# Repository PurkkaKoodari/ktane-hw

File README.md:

# KTaNE HW

This project is a hardware reimplementation of the game [Keep Talking and Nobody Explodes][ktane]. The game runs fully on the physical device and is controlled using a web interface over Wi-Fi. The project will be documented in this repository &ndash; expect the links below to be broken for the near future.

(TODO: insert photos here)

## Architecture

The hardware is built around a Raspberry Pi Zero W, which runs the main controller software, attached to a [backplane](doc/hardware/backplane.md) that provides power, connectivity and audio. The game's [modules](doc/hardware/modules.md) are built as independent devices, usually based on an Arduino Nano, which connect to the backplane using RJ-45 connectors (with a completely nonstandard usage of the pins).

The software can be divided into three parts: the [main controller](doc/software/main_controller.md), written in Python 3 using `asyncio` and [`websockets`][websockets]; the module software, written in C++ and built using [`arduino-cli`][arduino-cli]; and the Web interface, written using [Preact][preact]. In addition, one can run a [room server](doc/software/room_server.md), which supports room-scale audio and DMX lights and other effects.

## License

Unless otherwise noted, all software in this repository is licensed under the [MIT license](LICENSE); the hardware design files in `hardware/` are licensed under the [CERN-OHL-P v2](hardware/LICENSE); and the sounds in `sounds/` are licensed under CC-BY 3.0 (see [sounds/CREDITS.txt](sounds/CREDITS.txt) for authors).

This project is not in any way related to or endorsed by Steel Crate Games, nor does it include any assets from the original game. If you intend to build a copy of the project, please support them and [purchase a copy of the game][buy-ktane]!

[ktane]: http://www.keeptalkinggame.com/
[buy-ktane]: https://keeptalkinggame.com/#buynow
[websockets]: https://websockets.readthedocs.io/en/stable/intro.html
[arduino-cli]: https://arduino.github.io/arduino-cli/latest/commands/arduino-cli/
[preact]: https://preactjs.com/

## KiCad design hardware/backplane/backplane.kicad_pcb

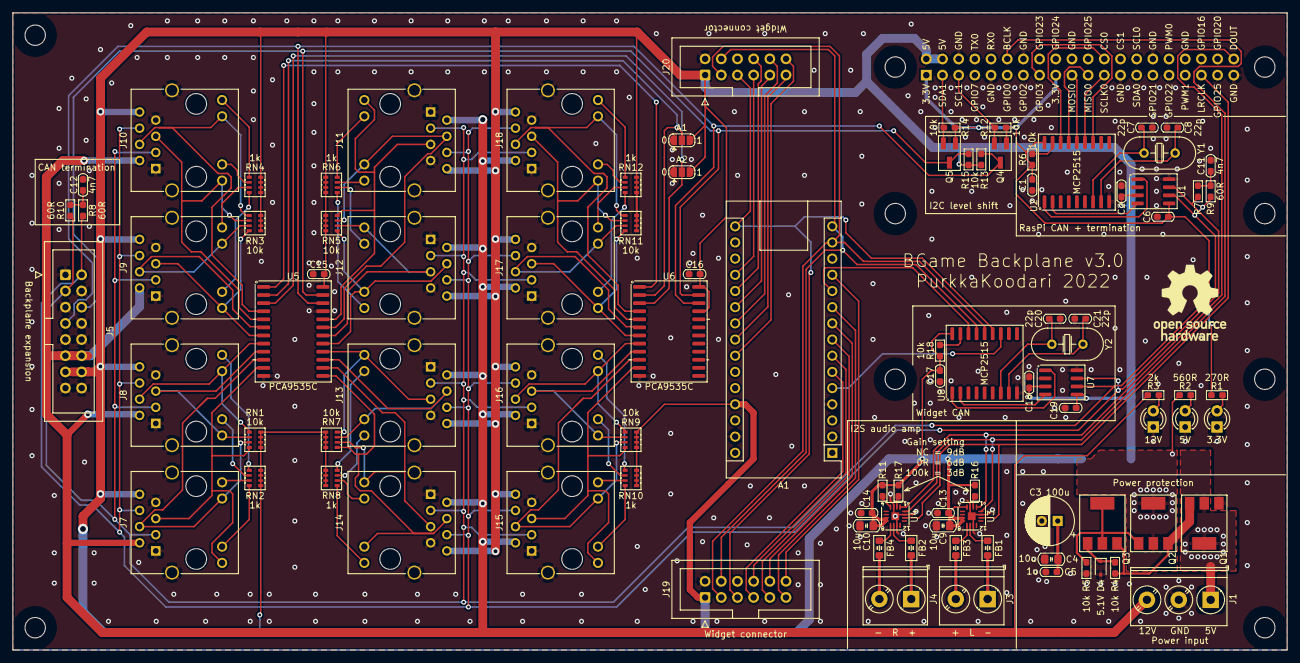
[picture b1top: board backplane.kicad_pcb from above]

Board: 2 copper layers, 200.0 x 100.0 mm, 103 parts (1 on the bottom side), 116 nets.

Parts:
A1: Arduino_Nano_v3.x; Arduino_Nano
C1, C2, C6, C13, C14, C15, C16, C17, C18, C19: 100n; C_0603_1608Metric_Pad1.08x0.95mm
C3: 100u; CP_Radial_D7.5mm_P2.50mm
C4, C9, C10: 10u; C_0805_2012Metric_Pad1.18x1.45mm
C5: 1u; C_0603_1608Metric_Pad1.08x0.95mm
C7, C8, C20, C21: 22p; C_0603_1608Metric_Pad1.08x0.95mm
C11, C12: 4n7; C_0603_1608Metric_Pad1.08x0.95mm
D1, D2, D3: LED; LED_D3.0mm
D4: BZX384-5V1; D_SOD-323
FB1, FB2, FB3, FB4: Ferrite_Bead; Ferrite_0805_2012Metric_Pad1.05x1.20mm_BigPads
H_RPI1, H_RPI2: RPi_HDR; MountingHole_3.2mm_M3
H_RPI3, H_RPI4: RPi_ZERO; MountingHole_3.2mm_M3
H_RPI5, H_RPI6: RPi_3; MountingHole_3.2mm_M3
J1: Screw_Terminal_01x03; TerminalBlock_Phoenix_PT-1,5-3-5.0-H_1x03_P5.00mm_Horizontal
J2: Raspberry_Pi_2_3; PinSocket_2x20_P2.54mm_Vertical
J3, J4: Screw_Terminal_01x02; TerminalBlock_Phoenix_PT-1,5-2-5.0-H_1x02_P5.00mm_Horizontal
J5: Conn_02x08_Odd_Even; IDC-Header_2x08_P2.54mm_Vertical
J7, J8, J9, J10, J11, J12, J13, J14, J15, J16, J17, J18: RJ45_LED_Shielded; RJ45_RCH5242CB
J19, J20: Conn_02x06_Odd_Even; IDC-Header_2x06_P2.54mm_Vertical
JP1: GPIO_A1; SolderJumper-3_P1.3mm_Open_RoundedPad1.0x1.5mm
JP2: GPIO_A2; SolderJumper-3_P1.3mm_Open_RoundedPad1.0x1.5mm
LOGO1: Logo_Open_Hardware_Small; OSHW-Logo_11.4x12mm_SilkScreen
Q1, Q2, Q3: ZXMP4A16G; SOT-223-3_TabPin2
Q4, Q5: Q_NMOS_GSD; SOT-23_Handsoldering
R1: 270R; R_0603_1608Metric_Pad1.05x0.95mm
R2: 560R; R_0603_1608Metric_Pad1.05x0.95mm
R3: 2k; R_0603_1608Metric_Pad1.05x0.95mm
R4, R5, R6, R12, R13, R14, R15, R18: 10k; R_0603_1608Metric_Pad1.05x0.95mm
R7, R8, R9, R10: 60R; R_0603_1608Metric_Pad1.05x0.95mm
R11: 330k; R_0603_1608Metric_Pad1.05x0.95mm
R16, R17: 100k; R_0603_1608Metric_Pad1.05x0.95mm
RN1, RN3, RN5, RN7, RN9, RN11: 10k; R_Array_Convex_4x0603
RN2, RN4, RN6, RN8, RN10, RN12: 1k; R_Array_Convex_4x0603
U1, U7: TJA1051T/3; SOIC-8_3.9x4.9mm_P1.27mm
U2, U8: MCP2515-xSO; SOIC-18W_7.5x11.6mm_P1.27mm
U3, U4: MAX98357AETE; TQFN-16-1EP_3x3mm_P0.5mm_EP1.23x1.23mm
U5, U6: PCA9535C; SOIC-24W_7.5x15.4mm_P1.27mm
Y1, Y2: 8MHz; Crystal_HC49-U_Vertical

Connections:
+3V3: C1.1, C6.1, J2.1 (3V3), J2.17 (3V3), Q4.1 (G), Q5.1 (G), R1.1, R6.1, R12.1, R14.1, U1.5 (VIO), U2.18 (VDD)
+5V: J1.1, Q1.2 (D)
+12V: J1.3, J5.11, J5.12, J7.2, J8.2, J9.2, J10.2, J11.2, J12.2, J13.2, J14.2, J15.2, J16.2, J17.2, J18.2, R3.1
/CAN_CS: J2.24 (~CE0/GPIO8), U2.16 (~CS)
/CAN_INT: J2.15 (GPIO22), U2.12 (~INT)
/GPIO_ADDR1: JP1.2 (C), U5.2 (A1), U6.2 (A1)
/GPIO_ADDR2: JP2.2 (C), U5.3 (A2), U6.3 (A2)
/GPIO_INT: U5.1 (~INT), U6.1 (~INT)
/MISO_3V3: J2.21 (MISO0/GPIO9), U2.15 (SO)
/MODULE_LOCATE_0: J7.4, J7.11, RN1.7 (R2.2), U5.10 (IO0_6)
/MODULE_LOCATE_1: J8.4, J8.11, RN1.5 (R4.2), U5.8 (IO0_4)
/MODULE_LOCATE_2: J9.4, J9.11, RN3.7 (R2.2), U5.6 (IO0_2)
/MODULE_LOCATE_3: J10.4, J10.11, RN3.5 (R4.2), U5.4 (IO0_0)
/MODULE_LOCATE_4: J11.4, J11.11, RN5.7 (R2.2), U5.19 (IO1_6)
/MODULE_LOCATE_5: J12.4, J12.11, RN5.5 (R4.2), U5.17 (IO1_4)
/MODULE_LOCATE_6: J13.4, J13.11, RN7.7 (R2.2), U5.15 (IO1_2)
/MODULE_LOCATE_7: J14.4, J14.11, RN7.5 (R4.2), U5.13 (IO1_0)
/MODULE_LOCATE_8: J15.4, J15.11, RN9.7 (R2.2), U6.10 (IO0_6)
/MODULE_LOCATE_9: J16.4, J16.11, RN9.5 (R4.2), U6.8 (IO0_4)
/MODULE_LOCATE_10: J17.4, J17.11, RN11.7 (R2.2), U6.6 (IO0_2)
/MODULE_LOCATE_11: J18.4, J18.11, RN11.5 (R4.2), U6.4 (IO0_0)
/MODULE_SENSE_0: J7.5, J7.9, RN1.8 (R1.2), U5.11 (IO0_7)
/MODULE_SENSE_1: J8.5, J8.9, RN1.6 (R3.2), U5.9 (IO0_5)
/MODULE_SENSE_2: J9.5, J9.9, RN3.8 (R1.2), U5.7 (IO0_3)
/MODULE_SENSE_3: J10.5, J10.9, RN3.6 (R3.2), U5.5 (IO0_1)
/MODULE_SENSE_4: J11.5, J11.9, RN5.8 (R1.2), U5.20 (IO1_7)
/MODULE_SENSE_5: J12.5, J12.9, RN5.6 (R3.2), U5.18 (IO1_5)
/MODULE_SENSE_6: J13.5, J13.9, RN7.8 (R1.2), U5.16 (IO1_3)
/MODULE_SENSE_7: J14.5, J14.9, RN7.6 (R3.2), U5.14 (IO1_1)
/MODULE_SENSE_8: J15.5, J15.9, RN9.8 (R1.2), U6.11 (IO0_7)
/MODULE_SENSE_9: J16.5, J16.9, RN9.6 (R3.2), U6.9 (IO0_5)
/MODULE_SENSE_10: J17.5, J17.9, RN11.8 (R1.2), U6.7 (IO0_3)
/MODULE_SENSE_11: J18.5, J18.9, RN11.6 (R3.2), U6.5 (IO0_1)
/MOSI_3V3: J2.19 (MOSI0/GPIO10), U2.14 (SI)
/PCM_BCLK: J2.12 (GPIO18/PWM0), U3.16 (BCLK), U4.16 (BCLK)
/PCM_DOUT: J2.40 (GPIO21/SCLK1), U3.1 (DIN), U4.1 (DIN)
/PCM_LRCLK: J2.35 (GPIO19/MISO1), U3.14 (LRCLK), U4.14 (LRCLK)
/SCL: J5.7, Q4.3 (D), R13.2, U5.22 (SCL), U6.22 (SCL)
/SCLK_3V3: J2.23 (SCLK0/GPIO11), U2.13 (SCK)
/SCL_3V3: J2.5 (SCL/GPIO3), Q4.2 (S), R12.2
/SDA: J5.6, Q5.3 (D), R15.2, U5.23 (SDA), U6.23 (SDA)
/SDA_3V3: J2.3 (SDA/GPIO2), Q5.2 (S), R14.2
/SPKR_L+: FB3.2, J3.2
/SPKR_L-: FB1.2, J3.1
/SPKR_R+: FB4.2, J4.2
/SPKR_R-: FB2.2, J4.1
/WIDGET_CAN_CS: A1.11 (D8), U8.16 (~CS)
/WIDGET_CAN_INT: A1.5 (D2), U8.12 (~INT)
/WIDGET_CS0: A1.6 (D3), J19.7
/WIDGET_CS1: A1.7 (D4), J19.8
/WIDGET_CS2: A1.8 (D5), J19.9
/WIDGET_CS3: A1.9 (D6), J19.10
/WIDGET_CS4: A1.10 (D7), J19.11
/WIDGET_CS5: A1.12 (D9), J19.12
/WIDGET_CS6: A1.19 (A0), J20.7
/WIDGET_CS7: A1.20 (A1), J20.8
/WIDGET_CS8: A1.21 (A2), J20.9
/WIDGET_CS9: A1.22 (A3), J20.10
/WIDGET_CS10: A1.23 (A4), J20.11
/WIDGET_CS11: A1.24 (A5), J20.12
/WIDGET_MISO: A1.15 (D12), J19.4, J20.4, U8.15 (SO)
/WIDGET_MOSI: A1.14 (D11), J19.3, J20.3, U8.14 (SI)
/WIDGET_SCLK: A1.16 (D13), J19.5, J20.5, U8.13 (SCK)
CAN_H: J5.2, J7.6, J8.6, J9.6, J10.6, J11.6, J12.6, J13.6, J14.6, J15.6, J16.6, J17.6, J18.6, R7.1, R8.1, U1.7 (CANH), U7.7 (CANH)
CAN_L: J5.3, J7.3, J8.3, J9.3, J10.3, J11.3, J12.3, J13.3, J14.3, J15.3, J16.3, J17.3, J18.3, R9.1, R10.1, U1.6 (CANL), U7.6 (CANL)
GND: A1.4 (GND), A1.29 (GND), C1.2, C2.2, C3.2, C4.2, C5.2, C6.2, C7.2, C8.2, C9.1, C10.1, C11.2, C12.2, C13.1, C14.1, C15.2, C16.2, C17.2, C18.2, C19.2, C20.2, C21.2, D1.1 (K), D2.1 (K), D3.1 (K), D4.2 (A), J1.2, J2.6 (GND), J2.9 (GND), J2.14 (GND), J2.20 (GND), J2.25 (GND), J2.30 (GND), J2.34 (GND), J2.39 (GND), J5.1, J5.4, J5.5, J5.8, J5.9, J5.10, J5.15, J5.16, J7.1, J7.7, J7.SH, J8.1, J8.7, J8.SH, J9.1, J9.7, J9.SH, J10.1, J10.7, J10.SH, J11.1, J11.7, J11.SH, J12.1, J12.7, J12.SH, J13.1, J13.7, J13.SH, J14.1, J14.7, J14.SH, J15.1, J15.7, J15.SH, J16.1, J16.7, J16.SH, J17.1, J17.7, J17.SH, J18.1, J18.7, J18.SH, J19.2, J20.2, JP1.1 (A), JP2.1 (A), Q1.1 (G), R5.2, U1.2 (GND), U1.8 (S), U2.9 (VSS), U3.3 (GND), U3.11 (GND), U3.15 (GND), U3.17 (EP), U4.3 (GND), U4.11 (GND), U4.15 (GND), U4.17 (EP), U5.12 (VSS), U5.21 (A0), U6.12 (VSS), U7.2 (GND), U7.8 (S), U8.9 (VSS)
unnamed: C7.1, U2.7 (OSC2), Y1.1
unnamed: C8.1, U2.8 (OSC1), Y1.2
unnamed: C11.1, R7.2, R9.2
unnamed: C12.1, R8.2, R10.2
unnamed: C20.1, U8.7 (OSC2), Y2.1
unnamed: C21.1, U8.8 (OSC1), Y2.2
unnamed: D1.2 (A), R1.2
unnamed: D2.2 (A), R2.2
unnamed: D3.2 (A), R3.2
unnamed: D4.1 (K), Q3.1 (G), R4.2
unnamed: FB1.1, U3.10 (OUTN)
unnamed: FB2.1, U4.10 (OUTN)
unnamed: FB3.1, U3.9 (OUTP)
unnamed: FB4.1, U4.9 (OUTP)
unnamed: J7.10, RN2.8 (R1.2)
unnamed: J7.12, RN2.7 (R2.2)
unnamed: J8.10, RN2.6 (R3.2)
unnamed: J8.12, RN2.5 (R4.2)
unnamed: J9.10, RN4.8 (R1.2)
unnamed: J9.12, RN4.7 (R2.2)
unnamed: J10.10, RN4.6 (R3.2)
unnamed: J10.12, RN4.5 (R4.2)
unnamed: J11.10, RN6.8 (R1.2)
unnamed: J11.12, RN6.7 (R2.2)
unnamed: J12.10, RN6.6 (R3.2)
unnamed: J12.12, RN6.5 (R4.2)
unnamed: J13.10, RN8.8 (R1.2)
unnamed: J13.12, RN8.7 (R2.2)
unnamed: J14.10, RN8.6 (R3.2)
unnamed: J14.12, RN8.5 (R4.2)
unnamed: J15.10, RN10.8 (R1.2)
unnamed: J15.12, RN10.7 (R2.2)
unnamed: J16.10, RN10.6 (R3.2)
unnamed: J16.12, RN10.5 (R4.2)
unnamed: J17.10, RN12.8 (R1.2)
unnamed: J17.12, RN12.7 (R2.2)
unnamed: J18.10, RN12.6 (R3.2)
unnamed: J18.12, RN12.5 (R4.2)
unnamed: Q1.3 (S), Q2.3 (S), Q3.3 (S), R4.1
unnamed: Q2.1 (G), Q3.2 (D), R5.1
unnamed: R6.2, U2.17 (~RESET)
unnamed: R11.2, U4.4 (~SD_MODE)
unnamed: R16.2, U3.2 (GAIN_SLOT)
unnamed: R17.2, U4.2 (GAIN_SLOT)
unnamed: R18.2, U8.17 (~RESET)
unnamed: U1.1 (TXD), U2.1 (TXCAN)
unnamed: U1.4 (RXD), U2.2 (RXCAN)
unnamed: U7.1 (TXD), U8.1 (TXCAN)
unnamed: U7.4 (RXD), U8.2 (RXCAN)
VCC: A1.27 (+5V), C2.1, C3.1, C4.1, C5.1, C9.2, C10.2, C13.2, C14.2, C15.1, C16.1, C17.1, C18.1, C19.1, J2.2 (5V), J2.4 (5V), J5.13, J5.14, J7.8, J8.8, J9.8, J10.8, J11.8, J12.8, J13.8, J14.8, J15.8, J16.8, J17.8, J18.8, J19.1, J20.1, JP1.3 (B), JP2.3 (B), Q2.2 (D), R2.1, R11.1, R13.1, R15.1, R16.1, R17.1, R18.1, RN1.1 (R1.1), RN1.2 (R2.1), RN1.3 (R3.1), RN1.4 (R4.1), RN2.1 (R1.1), RN2.2 (R2.1), RN2.3 (R3.1), RN2.4 (R4.1), RN3.1 (R1.1), RN3.2 (R2.1), RN3.3 (R3.1), RN3.4 (R4.1), RN4.1 (R1.1), RN4.2 (R2.1), RN4.3 (R3.1), RN4.4 (R4.1), RN5.1 (R1.1), RN5.2 (R2.1), RN5.3 (R3.1), RN5.4 (R4.1), RN6.1 (R1.1), RN6.2 (R2.1), RN6.3 (R3.1), RN6.4 (R4.1), RN7.1 (R1.1), RN7.2 (R2.1), RN7.3 (R3.1), RN7.4 (R4.1), RN8.1 (R1.1), RN8.2 (R2.1), RN8.3 (R3.1), RN8.4 (R4.1), RN9.1 (R1.1), RN9.2 (R2.1), RN9.3 (R3.1), RN9.4 (R4.1), RN10.1 (R1.1), RN10.2 (R2.1), RN10.3 (R3.1), RN10.4 (R4.1), RN11.1 (R1.1), RN11.2 (R2.1), RN11.3 (R3.1), RN11.4 (R4.1), RN12.1 (R1.1), RN12.2 (R2.1), RN12.3 (R3.1), RN12.4 (R4.1), U1.3 (VCC), U3.4 (~SD_MODE), U3.7 (VDD), U3.8 (VDD), U4.7 (VDD), U4.8 (VDD), U5.24 (VDD), U6.21 (A0), U6.24 (VDD), U7.3 (VCC), U7.5 (VIO), U8.18 (VDD)

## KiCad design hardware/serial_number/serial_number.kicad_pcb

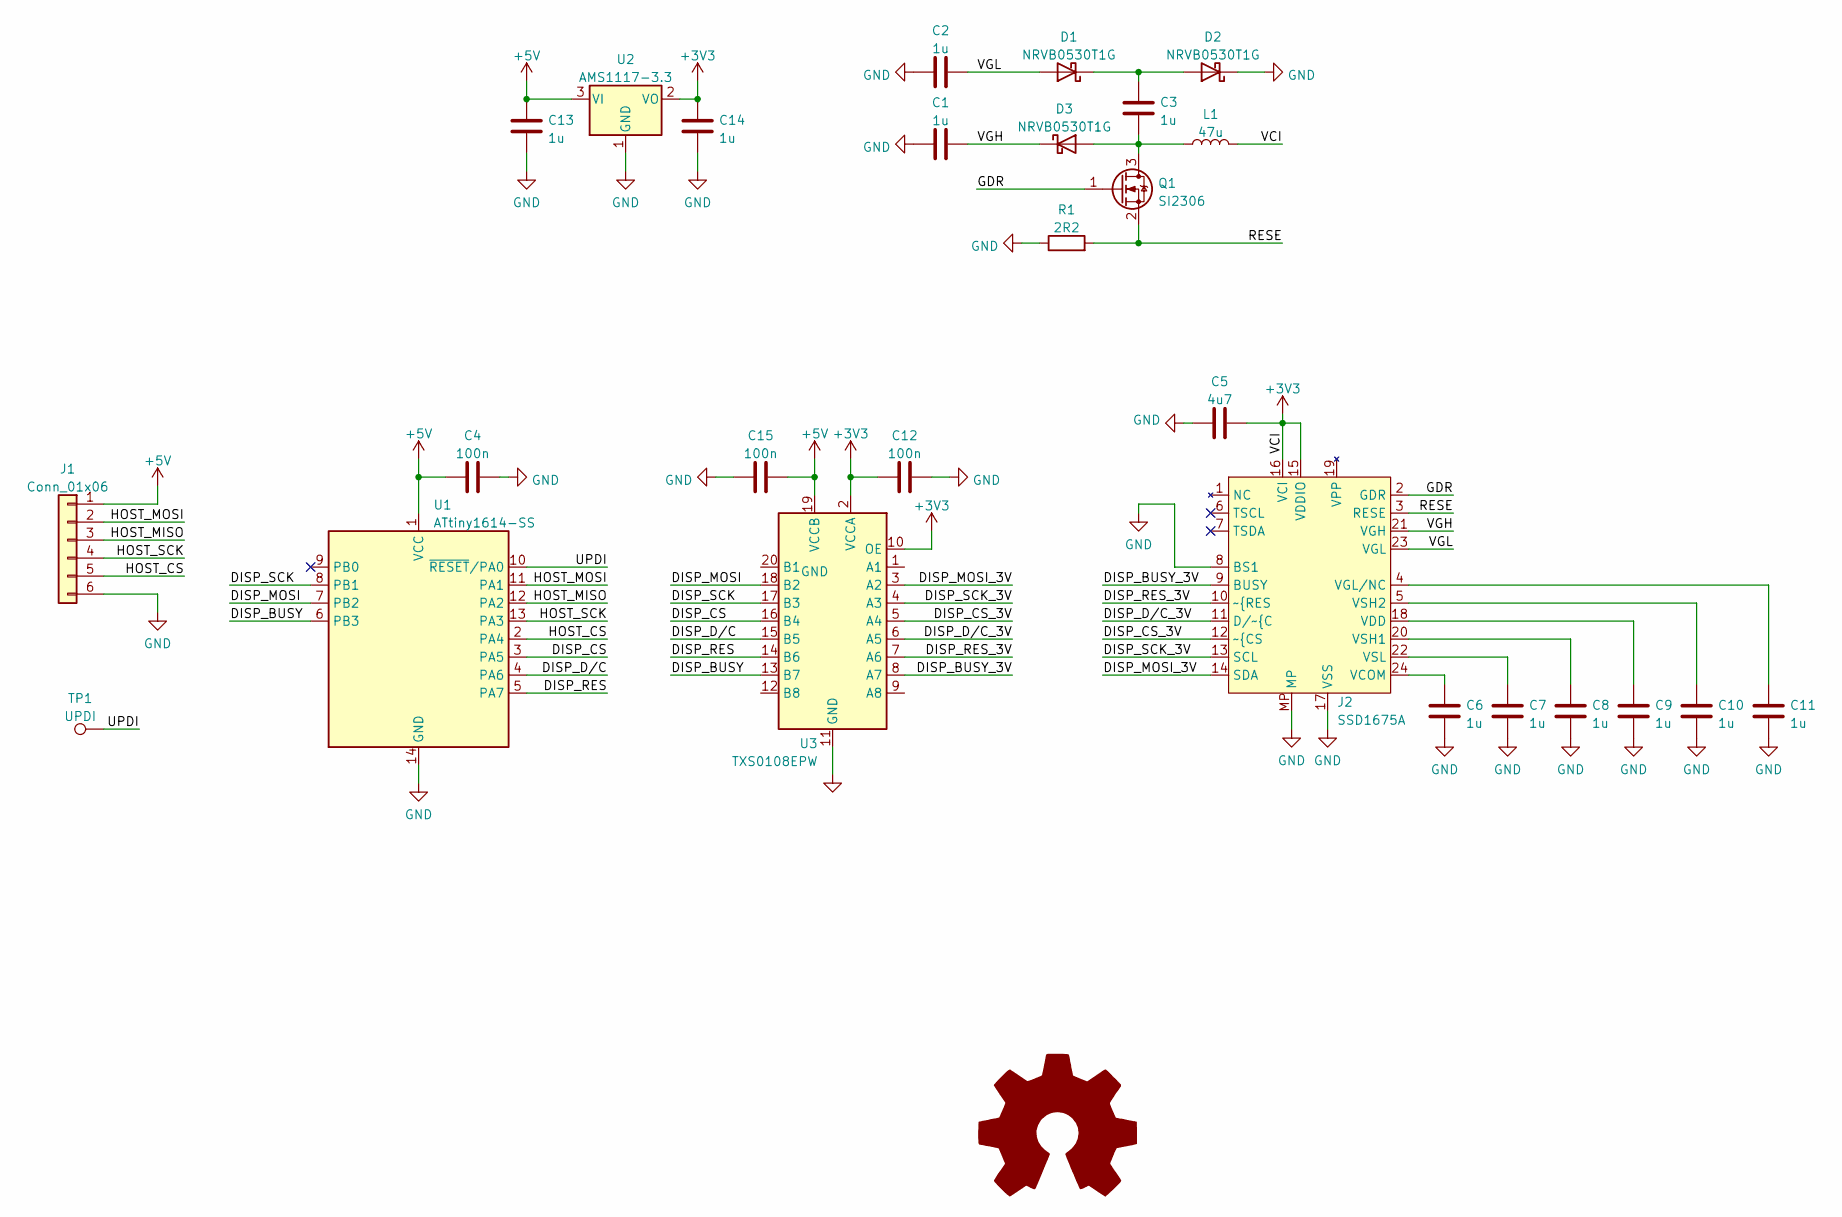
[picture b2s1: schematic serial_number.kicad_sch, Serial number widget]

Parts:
C1, C2, C3, C6, C7, C8, C9, C10, C11, C13, C14: 1u; C_0603_1608Metric_Pad1.08x0.95mm
C4, C12, C15: 100n; C_0603_1608Metric_Pad1.08x0.95mm
C5: 4u7; C_0603_1608Metric_Pad1.08x0.95mm
D1, D2, D3: NRVB0530T1G; D_SOD-123
J1: Conn_01x06; PinHeader_1x06_P2.54mm_Vertical
J2: SSD1675A; ER-CON24HT-1
L1: 47u; L_Taiyo-Yuden_NR-40xx
LOGO1: Logo_Open_Hardware_Large; OSHW-Logo_11.4x12mm_SilkScreen
Q1: SI2306; SOT-23_Handsoldering
R1: 2R2; R_0805_2012Metric_Pad1.20x1.40mm
TP1: UPDI; TestPoint_Pad_D2.5mm
U1: ATtiny1614-SS; SOIC-14_3.9x8.7mm_P1.27mm
U2: AMS1117-3.3; SOT-223-3_TabPin2
U3: TXS0108EPW; TSSOP-20_4.4x6.5mm_P0.65mm

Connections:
+3V3: C5.2, C12.1, C14.2, J2.15 (VDDIO), J2.16 (VCI), L1.2, U2.2 (VO), U3.2 (VCCA), U3.10 (OE)
+5V: C4.1, C13.2, C15.1, J1.1, U1.1 (VCC), U2.3 (VI), U3.19 (VCCB)
/DISP_BUSY: U1.6 (PB3), U3.13 (B7)
/DISP_BUSY_3V: J2.9 (BUSY), U3.8 (A7)
/DISP_CS: U1.3 (PA5), U3.16 (B4)
/DISP_CS_3V: J2.12 (~{CS), U3.5 (A4)
/DISP_D/C: U1.4 (PA6), U3.15 (B5)
/DISP_D/C_3V: J2.11 (D/~{C), U3.6 (A5)
/DISP_MOSI: U1.7 (PB2), U3.18 (B2)
/DISP_MOSI_3V: J2.14 (SDA), U3.3 (A2)
/DISP_RES: U1.5 (PA7), U3.14 (B6)
/DISP_RES_3V: J2.10 (~{RES), U3.7 (A6)
/DISP_SCK: U1.8 (PB1), U3.17 (B3)
/DISP_SCK_3V: J2.13 (SCL), U3.4 (A3)
/GDR: J2.2 (GDR), Q1.1 (G)
/HOST_CS: J1.5, U1.2 (PA4)
/HOST_MISO: J1.3, U1.12 (PA2)
/HOST_MOSI: J1.2, U1.11 (PA1)
/HOST_SCK: J1.4, U1.13 (PA3)
/RESE: J2.3 (RESE), Q1.2 (S), R1.2
/UPDI: TP1.1, U1.10 (~RESET/PA0)
/VGH: C1.2, D3.1 (K), J2.21 (VGH)
/VGL: C2.2, D1.2 (A), J2.23 (VGL)
GND: C1.1, C2.1, C4.2, C5.1, C6.1, C7.1, C8.1, C9.1, C10.1, C11.1, C12.2, C13.1, C14.1, C15.2, D2.1 (K), J1.6, J2.8 (BS1), J2.17 (VSS), J2.MP, R1.1, U1.14 (GND), U2.1 (GND), U3.11 (GND)
unnamed: C3.1, D1.1 (K), D2.2 (A)
unnamed: C3.2, D3.2 (A), L1.1, Q1.3 (D)
unnamed: C6.2, J2.24 (VCOM)
unnamed: C7.2, J2.22 (VSL)
unnamed: C8.2, J2.20 (VSH1)
unnamed: C9.2, J2.18 (VDD)
unnamed: C10.2, J2.5 (VSH2)
unnamed: C11.2, J2.4 (VGL/NC)

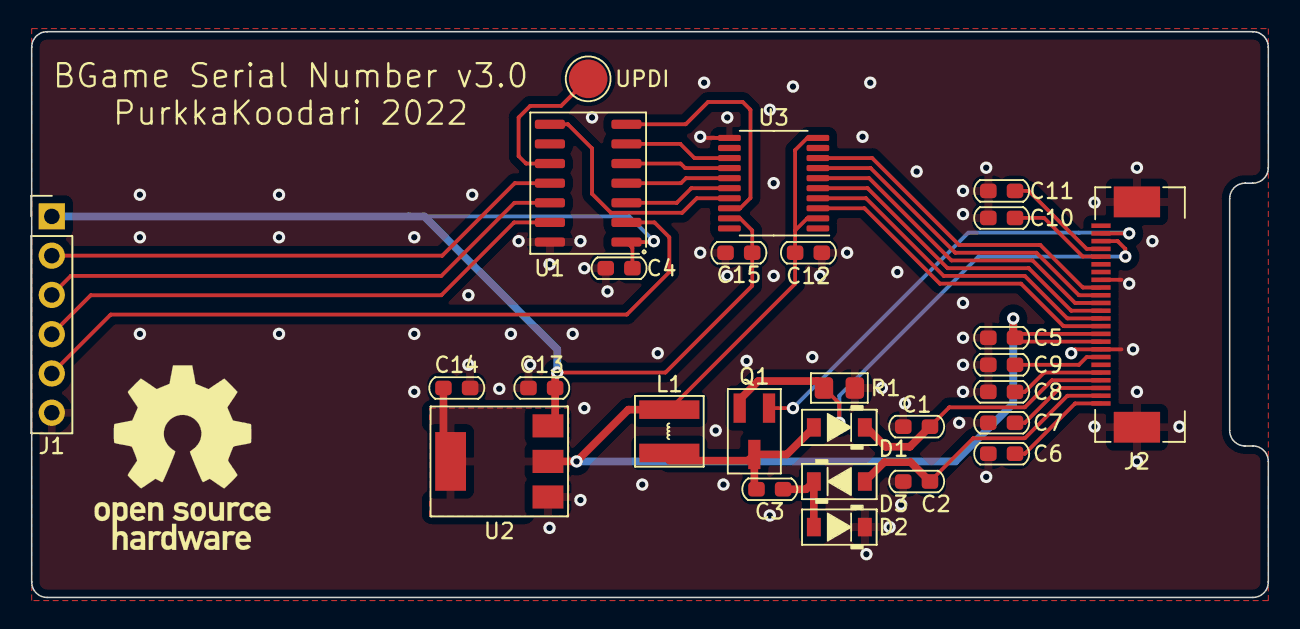
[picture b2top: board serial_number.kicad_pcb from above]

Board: 2 copper layers, 80.0 x 36.6 mm, 28 parts (0 on the bottom side), 32 nets.

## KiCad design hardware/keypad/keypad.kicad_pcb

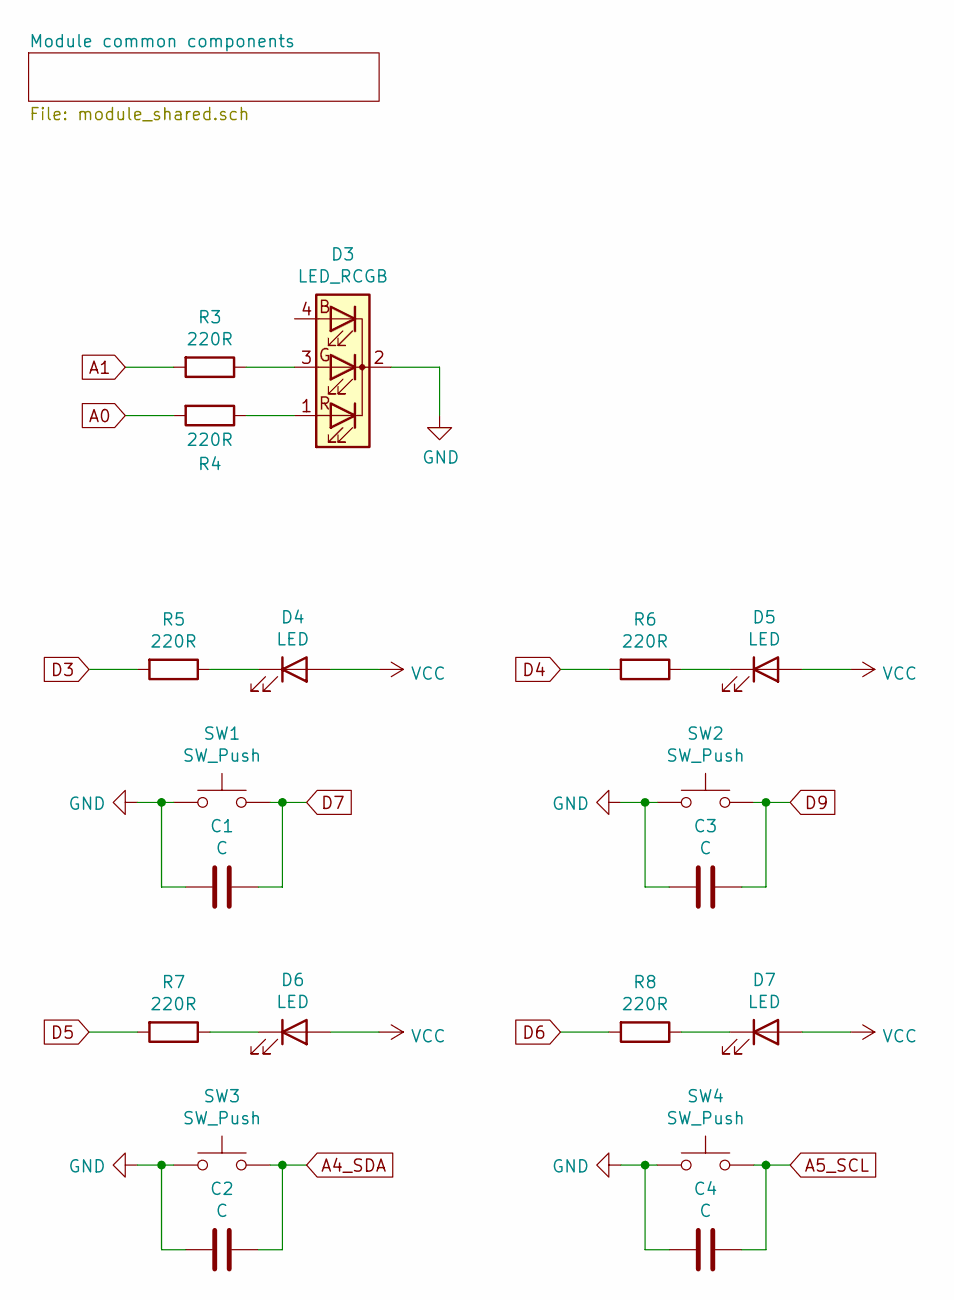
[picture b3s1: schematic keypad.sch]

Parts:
C1, C2, C3, C4: C; C_0805_2012Metric_Pad1.15x1.40mm_HandSolder
D3: LED_RCGB; LED_D5.0mm-4_RGB_Wide_Pins
D4, D5, D6, D7: LED; LED_D3.0mm
R3, R4, R5, R6, R7, R8: 220R; R_0603_1608Metric_Pad1.05x0.95mm_HandSolder
SW1, SW2, SW3, SW4: SW_Push; SW_Cherry_MX_1.00u_PCB

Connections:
A0: R4.2; also elsewhere on the board
A1: R3.2; also elsewhere on the board
A4_SDA: C2.1, SW3.2; also elsewhere on the board
A5_SCL: C4.1, SW4.2; also elsewhere on the board
D3: R5.2; also elsewhere on the board
D4: R6.2; also elsewhere on the board
D5: R7.2; also elsewhere on the board
D6: R8.2; also elsewhere on the board
D7: C1.1, SW1.2; also elsewhere on the board
D9: C3.1, SW2.2; also elsewhere on the board
GND: C1.2, C2.2, C3.2, C4.2, D3.2 (K), SW1.1, SW2.1, SW3.1, SW4.1; also elsewhere on the board
unnamed: D3.1 (RA), R4.1
unnamed: D3.3 (GA), R3.1
unnamed: D4.1 (K), R5.1
unnamed: D5.1 (K), R6.1
unnamed: D6.1 (K), R7.1
unnamed: D7.1 (K), R8.1
VCC: D4.2 (A), D5.2 (A), D6.2 (A), D7.2 (A); also elsewhere on the board

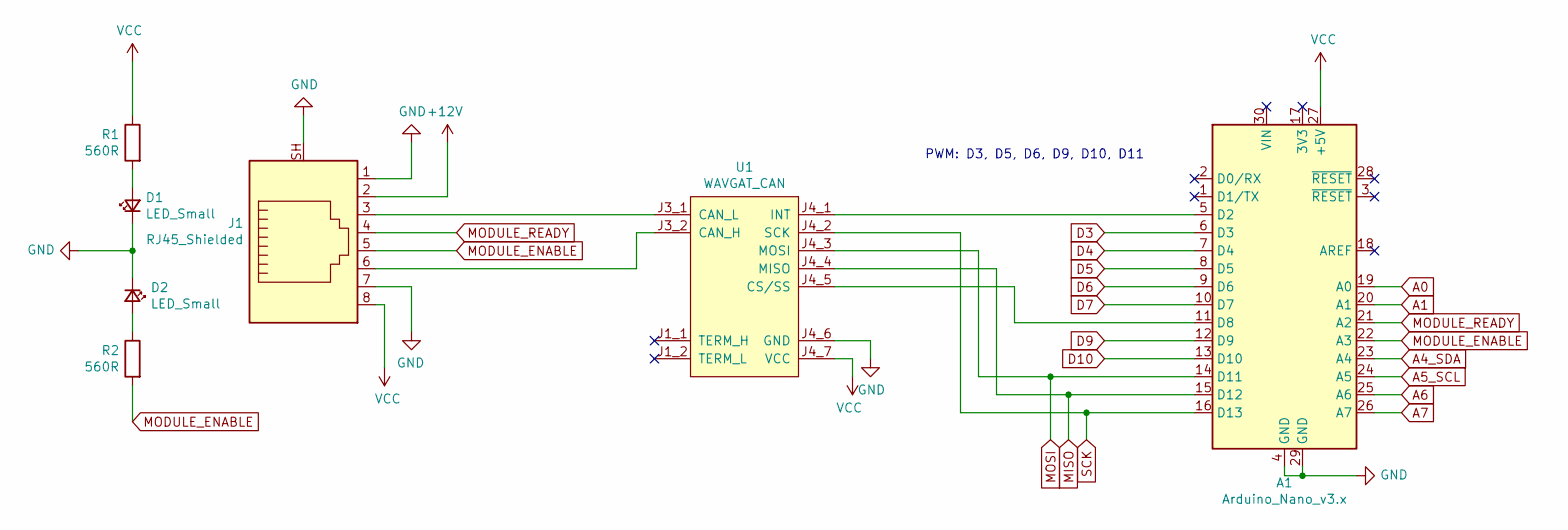
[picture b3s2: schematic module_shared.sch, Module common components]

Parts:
A1: Arduino_Nano_v3.x; Arduino_Nano
D1, D2: LED_Small; LED_D3.0mm
J1: RJ45_Shielded; RJ45_5224
R1, R2: 560R; R_0603_1608Metric_Pad1.05x0.95mm_HandSolder
U1: WAVGAT_CAN

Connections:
+12V: J1.2
A0: A1.19 (A0); also elsewhere on the board
A1: A1.20 (A1); also elsewhere on the board
A4_SDA: A1.23 (A4); also elsewhere on the board
A5_SCL: A1.24 (A5); also elsewhere on the board
A6: A1.25 (A6)
A7: A1.26 (A7)
D3: A1.6 (D3); also elsewhere on the board
D4: A1.7 (D4); also elsewhere on the board
D5: A1.8 (D5); also elsewhere on the board
D6: A1.9 (D6); also elsewhere on the board
D7: A1.10 (D7); also elsewhere on the board
D9: A1.12 (D9); also elsewhere on the board
D10: A1.13 (D10)
GND: A1.4 (GND), A1.29 (GND), D1.1 (K), D2.1 (K), J1.1, J1.7, J1.SH, U1.J4_6 (GND); also elsewhere on the board
MISO: A1.15 (D12), U1.J4_4 (MISO)
MODULE_ENABLE: A1.22 (A3), J1.5, R2.2
MODULE_READY: A1.21 (A2), J1.4
MOSI: A1.14 (D11), U1.J4_3 (MOSI)
unnamed: A1.5 (D2), U1.J4_1 (INT)
unnamed: A1.11 (D8), U1.J4_5 (CS/SS)
unnamed: D1.2 (A), R1.2
unnamed: D2.2 (A), R2.1
unnamed: J1.3, U1.J3_1 (CAN_L)
unnamed: J1.6, U1.J3_2 (CAN_H)
SCK: A1.16 (D13), U1.J4_2 (SCK)
VCC: A1.27 (+5V), J1.8, R1.1, U1.J4_7 (VCC); also elsewhere on the board

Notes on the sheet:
PWM: D3, D5, D6, D9, D10, D11

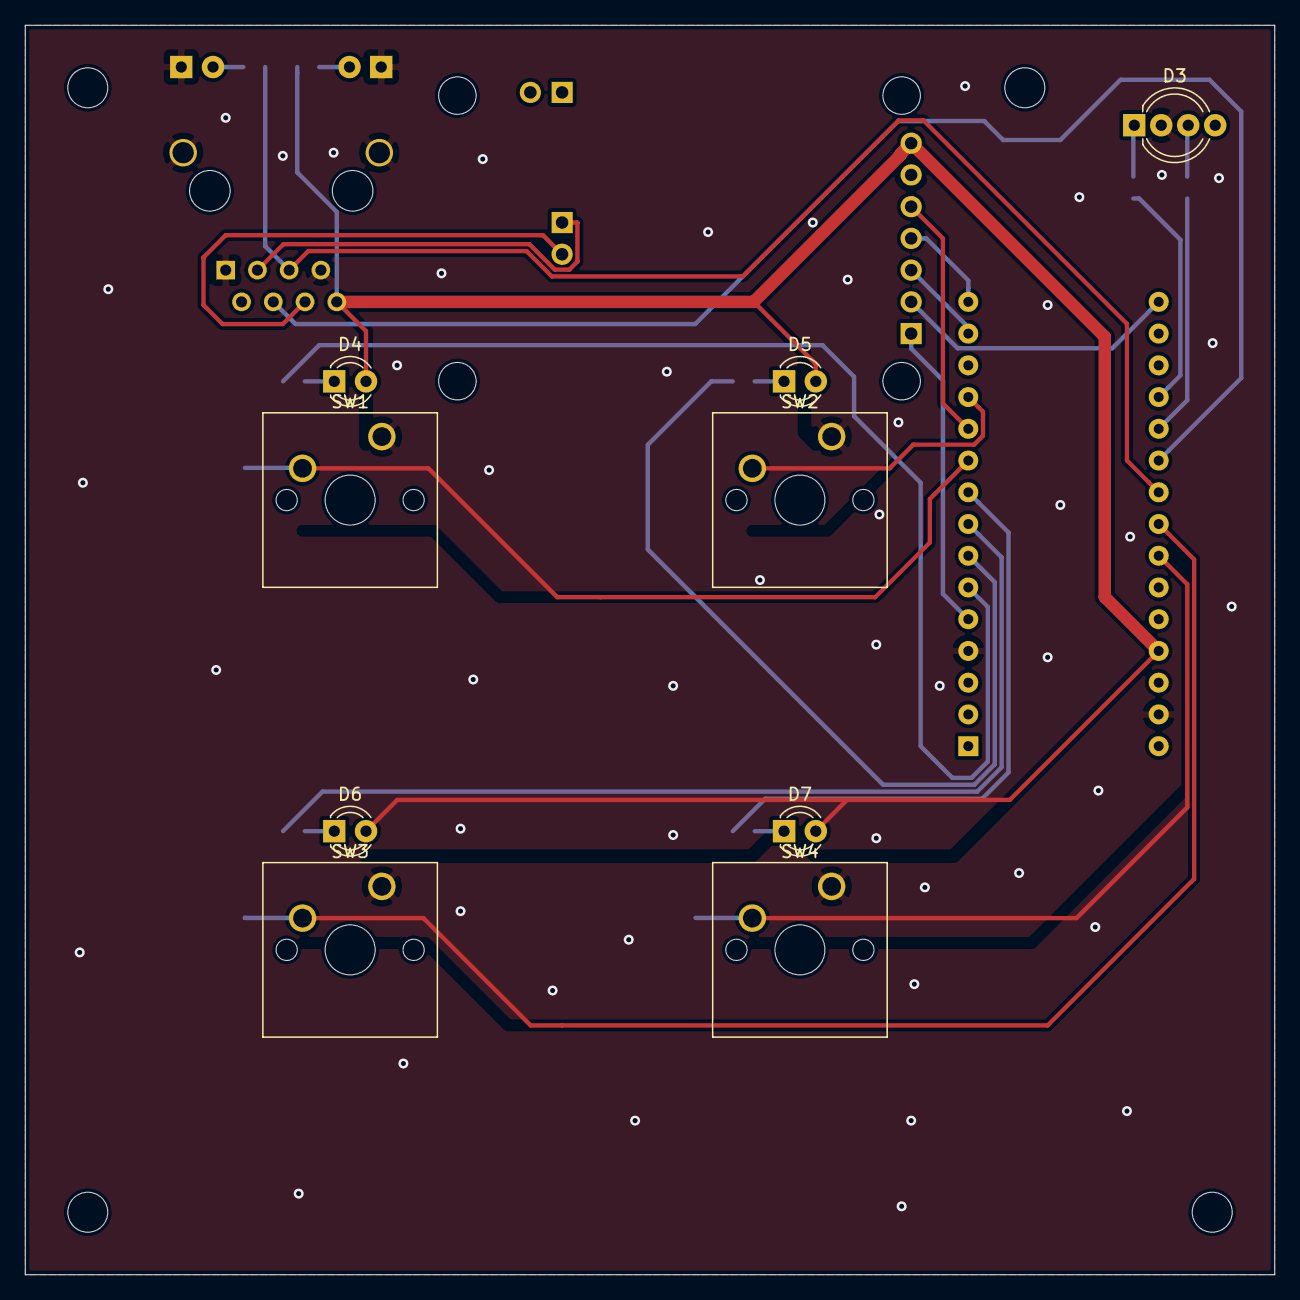
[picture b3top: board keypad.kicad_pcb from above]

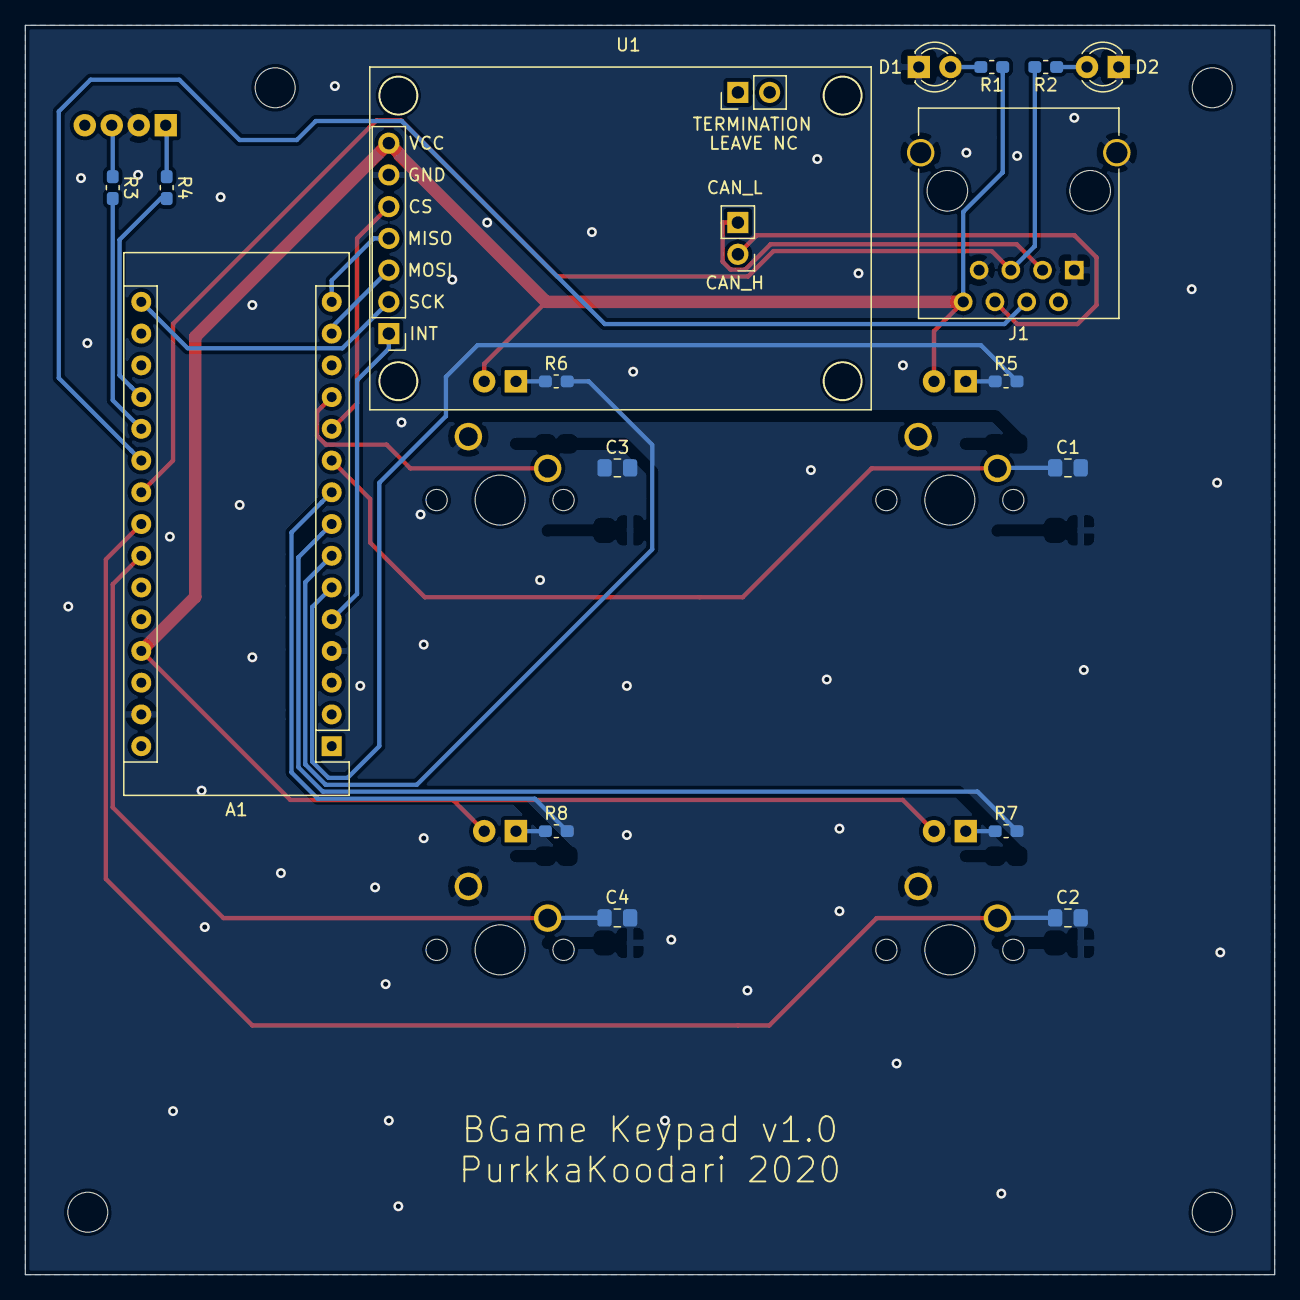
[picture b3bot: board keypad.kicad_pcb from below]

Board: 2 copper layers, 100.0 x 100.0 mm, 26 parts (17 on the bottom side), 29 nets.

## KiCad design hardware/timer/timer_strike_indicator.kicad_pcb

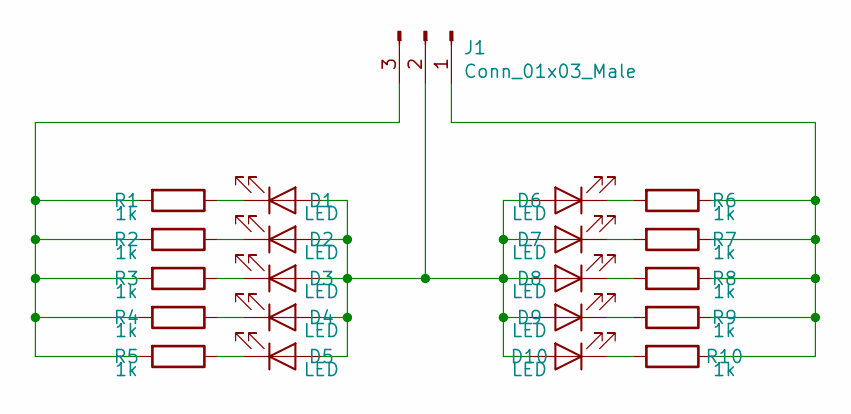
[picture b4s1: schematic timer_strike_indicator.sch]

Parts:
D1, D2, D3, D4, D5, D6, D7, D8, D9, D10: LED; LED_D3.0mm
J1: Conn_01x03_Male; PinHeader_1x03_P2.54mm_Vertical
R1, R2, R3, R4, R5, R6, R7, R8, R9, R10: 1k; R_0603_1608Metric_Pad1.05x0.95mm_HandSolder

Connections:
unnamed: D1.1 (K), R1.1
unnamed: D1.2 (A), D2.2 (A), D3.2 (A), D4.2 (A), D5.2 (A), D6.2 (A), D7.2 (A), D8.2 (A), D9.2 (A), D10.2 (A), J1.2
unnamed: D2.1 (K), R2.1
unnamed: D3.1 (K), R3.1
unnamed: D4.1 (K), R4.1
unnamed: D5.1 (K), R5.1
unnamed: D6.1 (K), R6.2
unnamed: D7.1 (K), R7.2
unnamed: D8.1 (K), R8.2
unnamed: D9.1 (K), R9.2
unnamed: D10.1 (K), R10.2
unnamed: J1.1, R6.1, R7.1, R8.1, R9.1, R10.1
unnamed: J1.3, R1.2, R2.2, R3.2, R4.2, R5.2

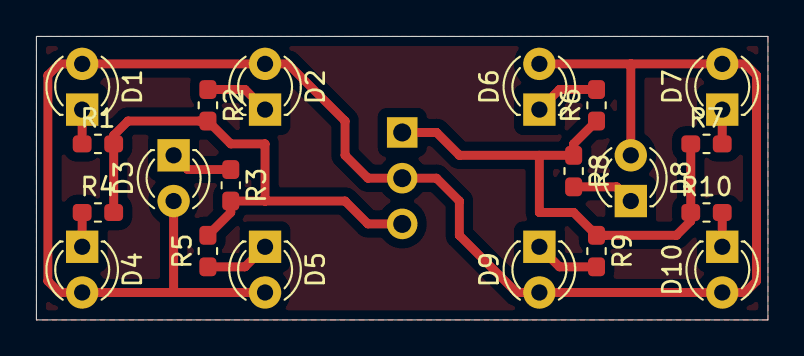
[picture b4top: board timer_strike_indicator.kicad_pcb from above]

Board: 2 copper layers, 40.6 x 15.7 mm, 21 parts (1 on the bottom side), 13 nets.
